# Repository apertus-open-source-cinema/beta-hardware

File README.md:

View this project on [CADLAB.io](https://cadlab.io/project/23633). 

# AXIOM Beta Hardware
[Axiom beta enclosure concept art](https://www.apertus.org/)

This repository contains all the information and files related to the hardware of the AXIOM Beta.

The [AXIOM Beta](https://www.apertus.org/axiom-beta) is an open source, open hardware, professional-grade digital film camera made by [apertus°](https://www.apertus.org/). It is designed to be modular e.g. interchangeable sensor front end etc. and supports recording at 4K resolution.

Introduction to [camera structure](https://www.apertus.org/axiom-beta-modularity).

## Contributing
If you would like to participate in this project, please see the following links:

[apertus° Labs](https://lab.apertus.org/project/view/4/) - Tasks, discussions, etc.
Project [Wiki](https://wiki.apertus.org/index.php/Main_Page) - User manuals, BOMs etc.
Programming languages and contact [methods](https://wiki.apertus.org/index.php/How_to_Contribute).
Useful [Links](https://wiki.apertus.org/index.php/Useful_Links).

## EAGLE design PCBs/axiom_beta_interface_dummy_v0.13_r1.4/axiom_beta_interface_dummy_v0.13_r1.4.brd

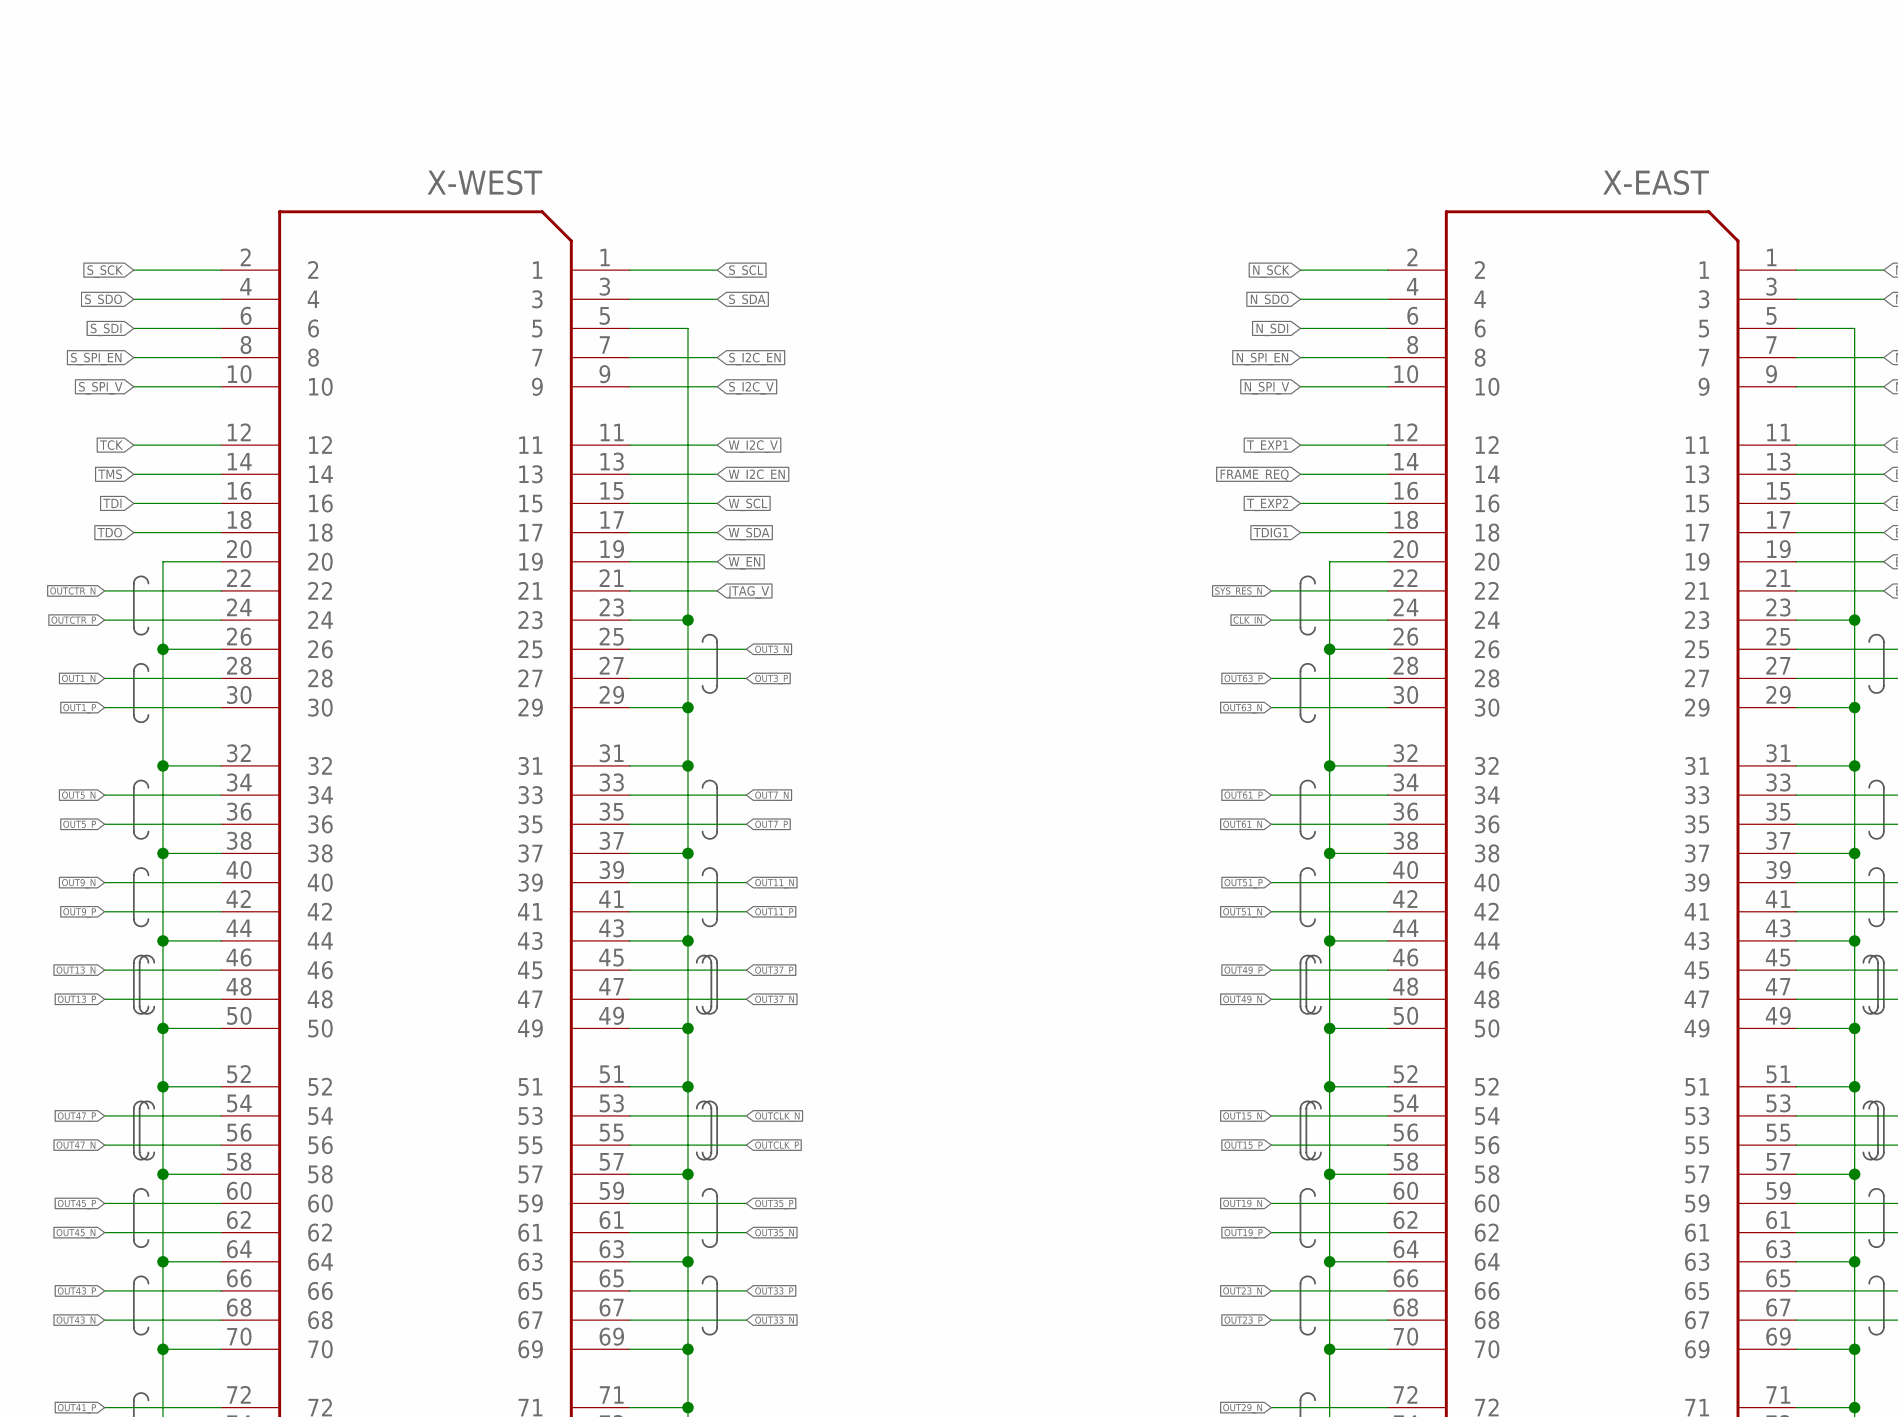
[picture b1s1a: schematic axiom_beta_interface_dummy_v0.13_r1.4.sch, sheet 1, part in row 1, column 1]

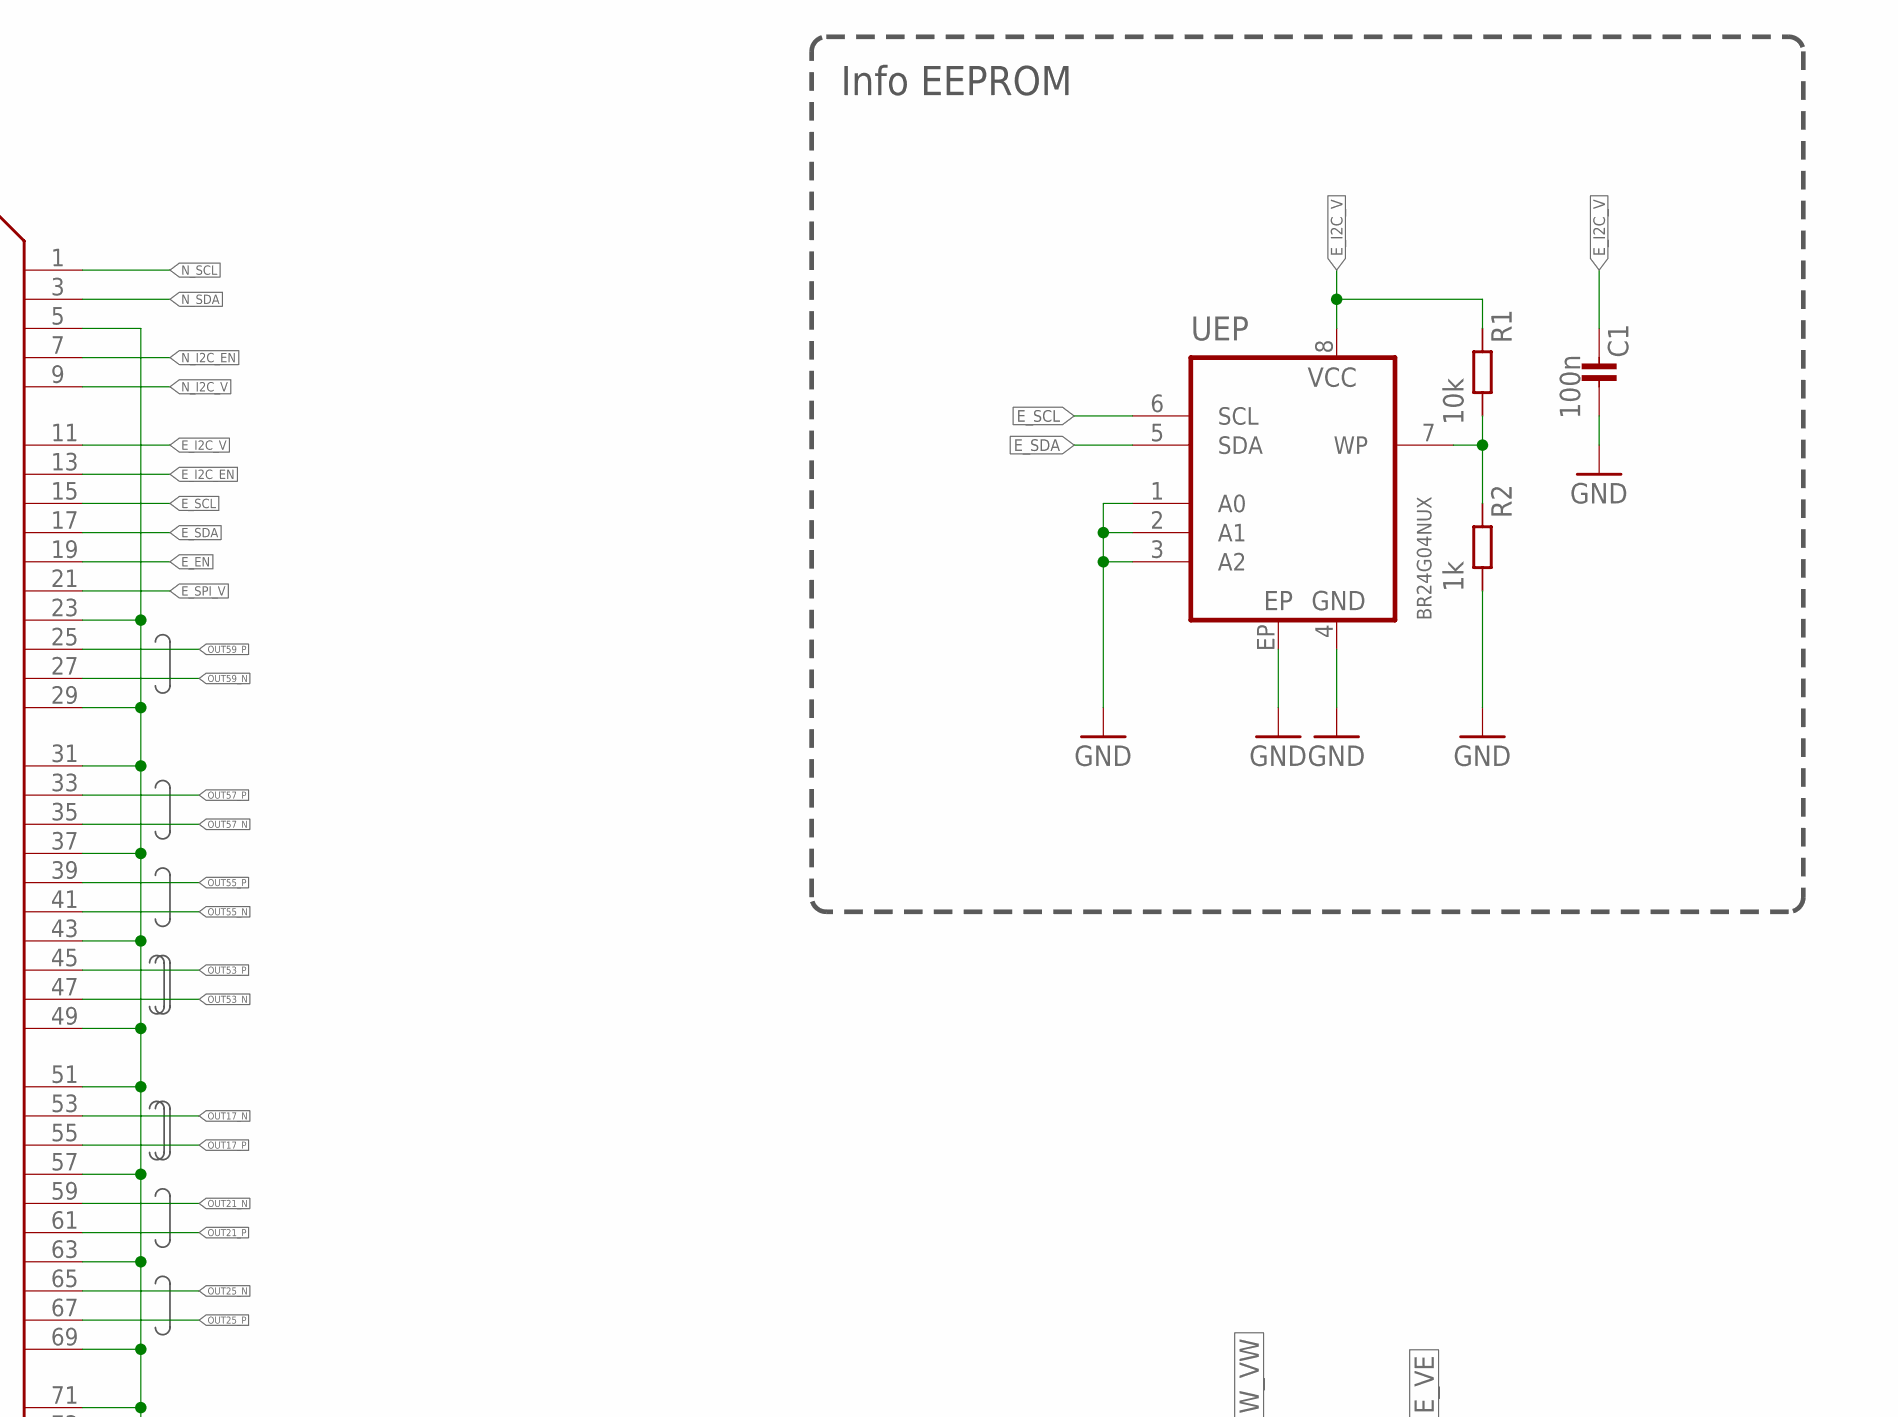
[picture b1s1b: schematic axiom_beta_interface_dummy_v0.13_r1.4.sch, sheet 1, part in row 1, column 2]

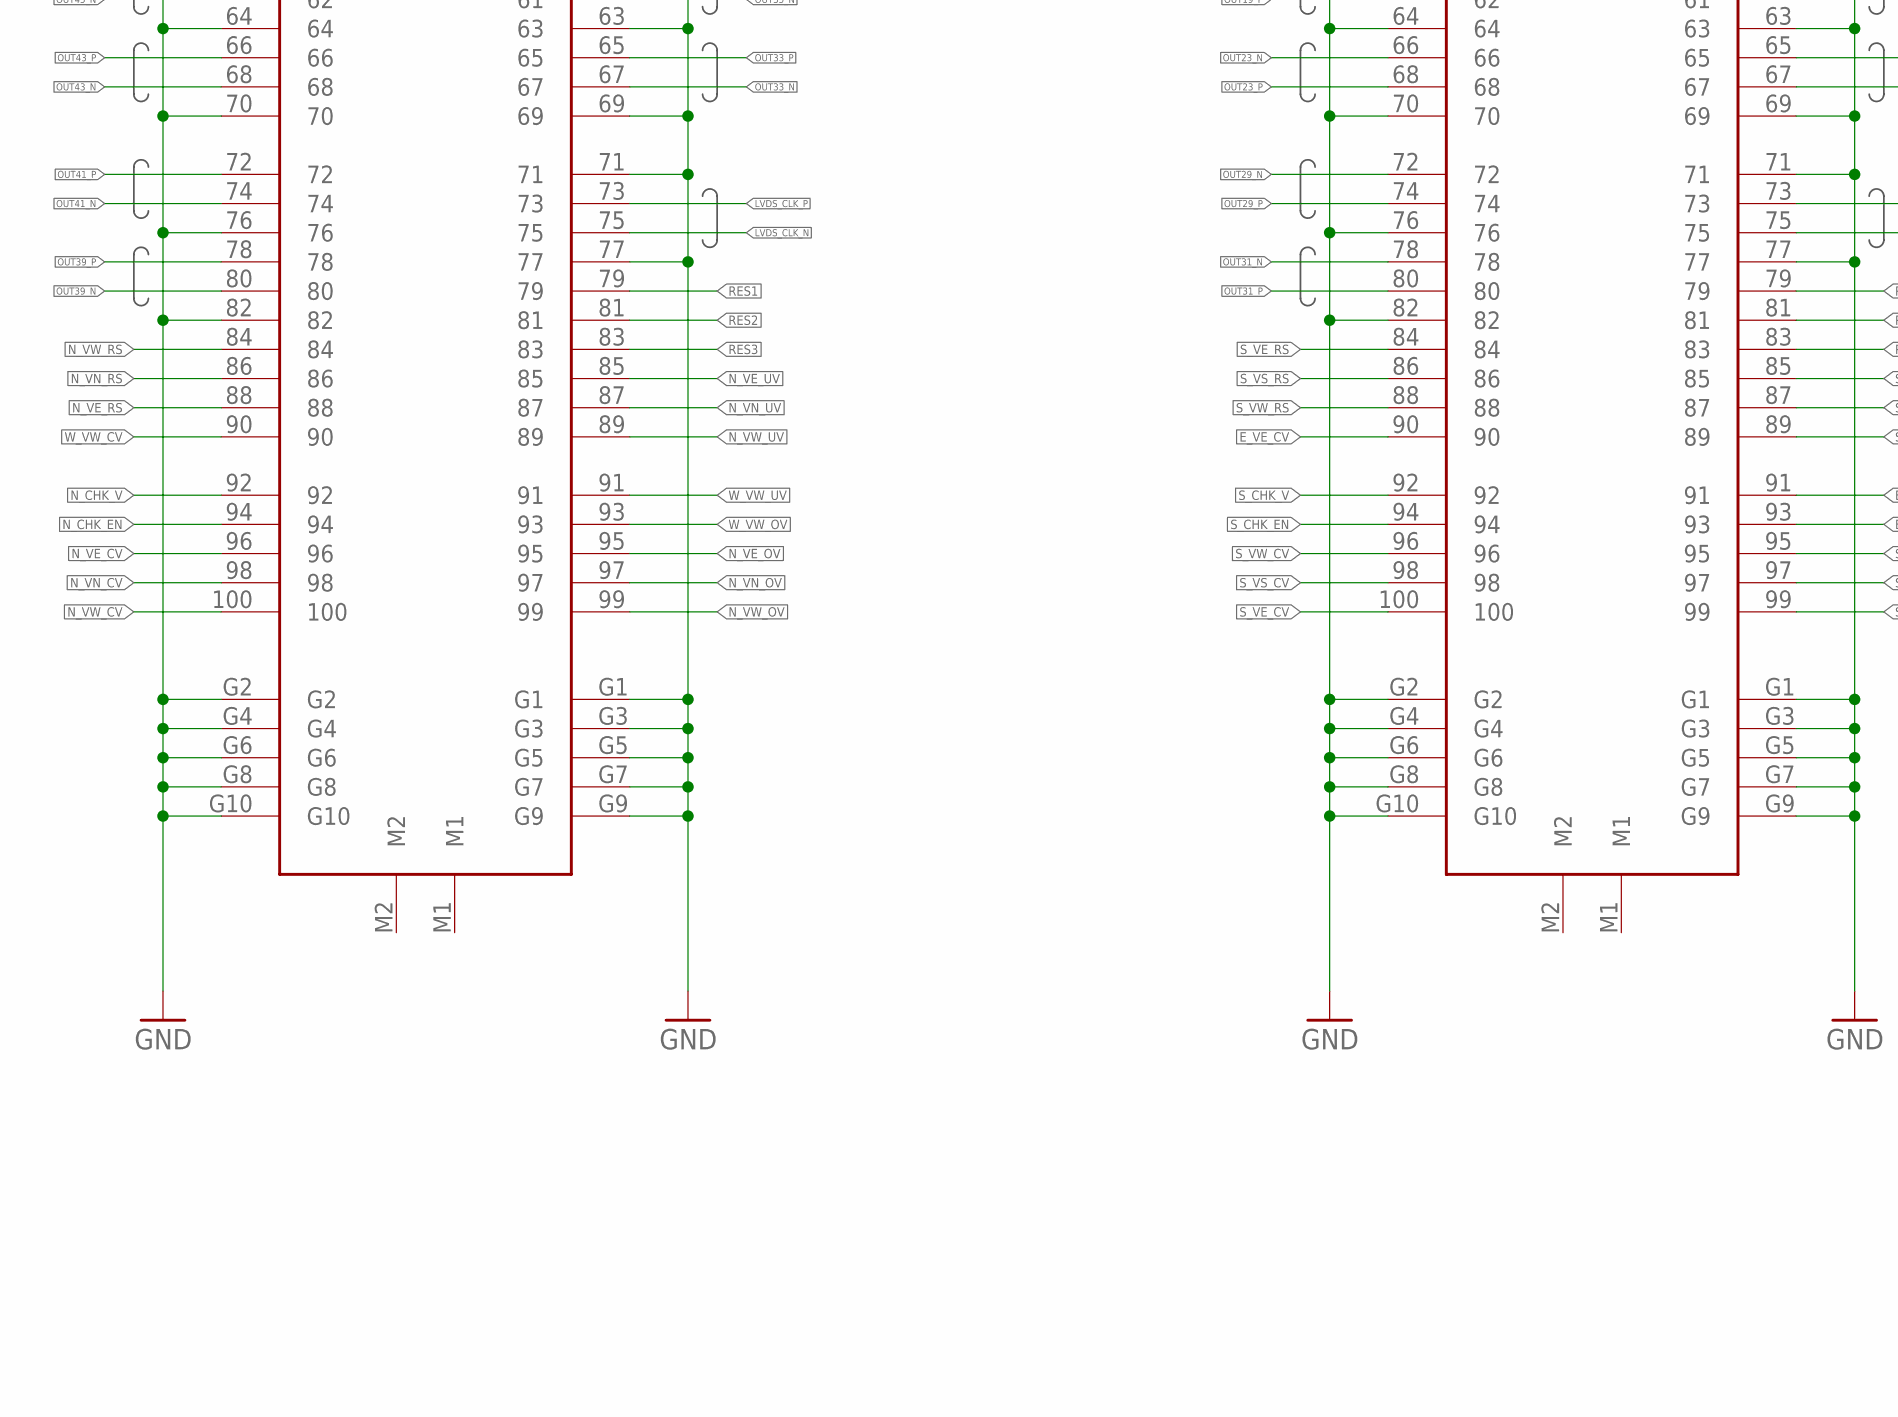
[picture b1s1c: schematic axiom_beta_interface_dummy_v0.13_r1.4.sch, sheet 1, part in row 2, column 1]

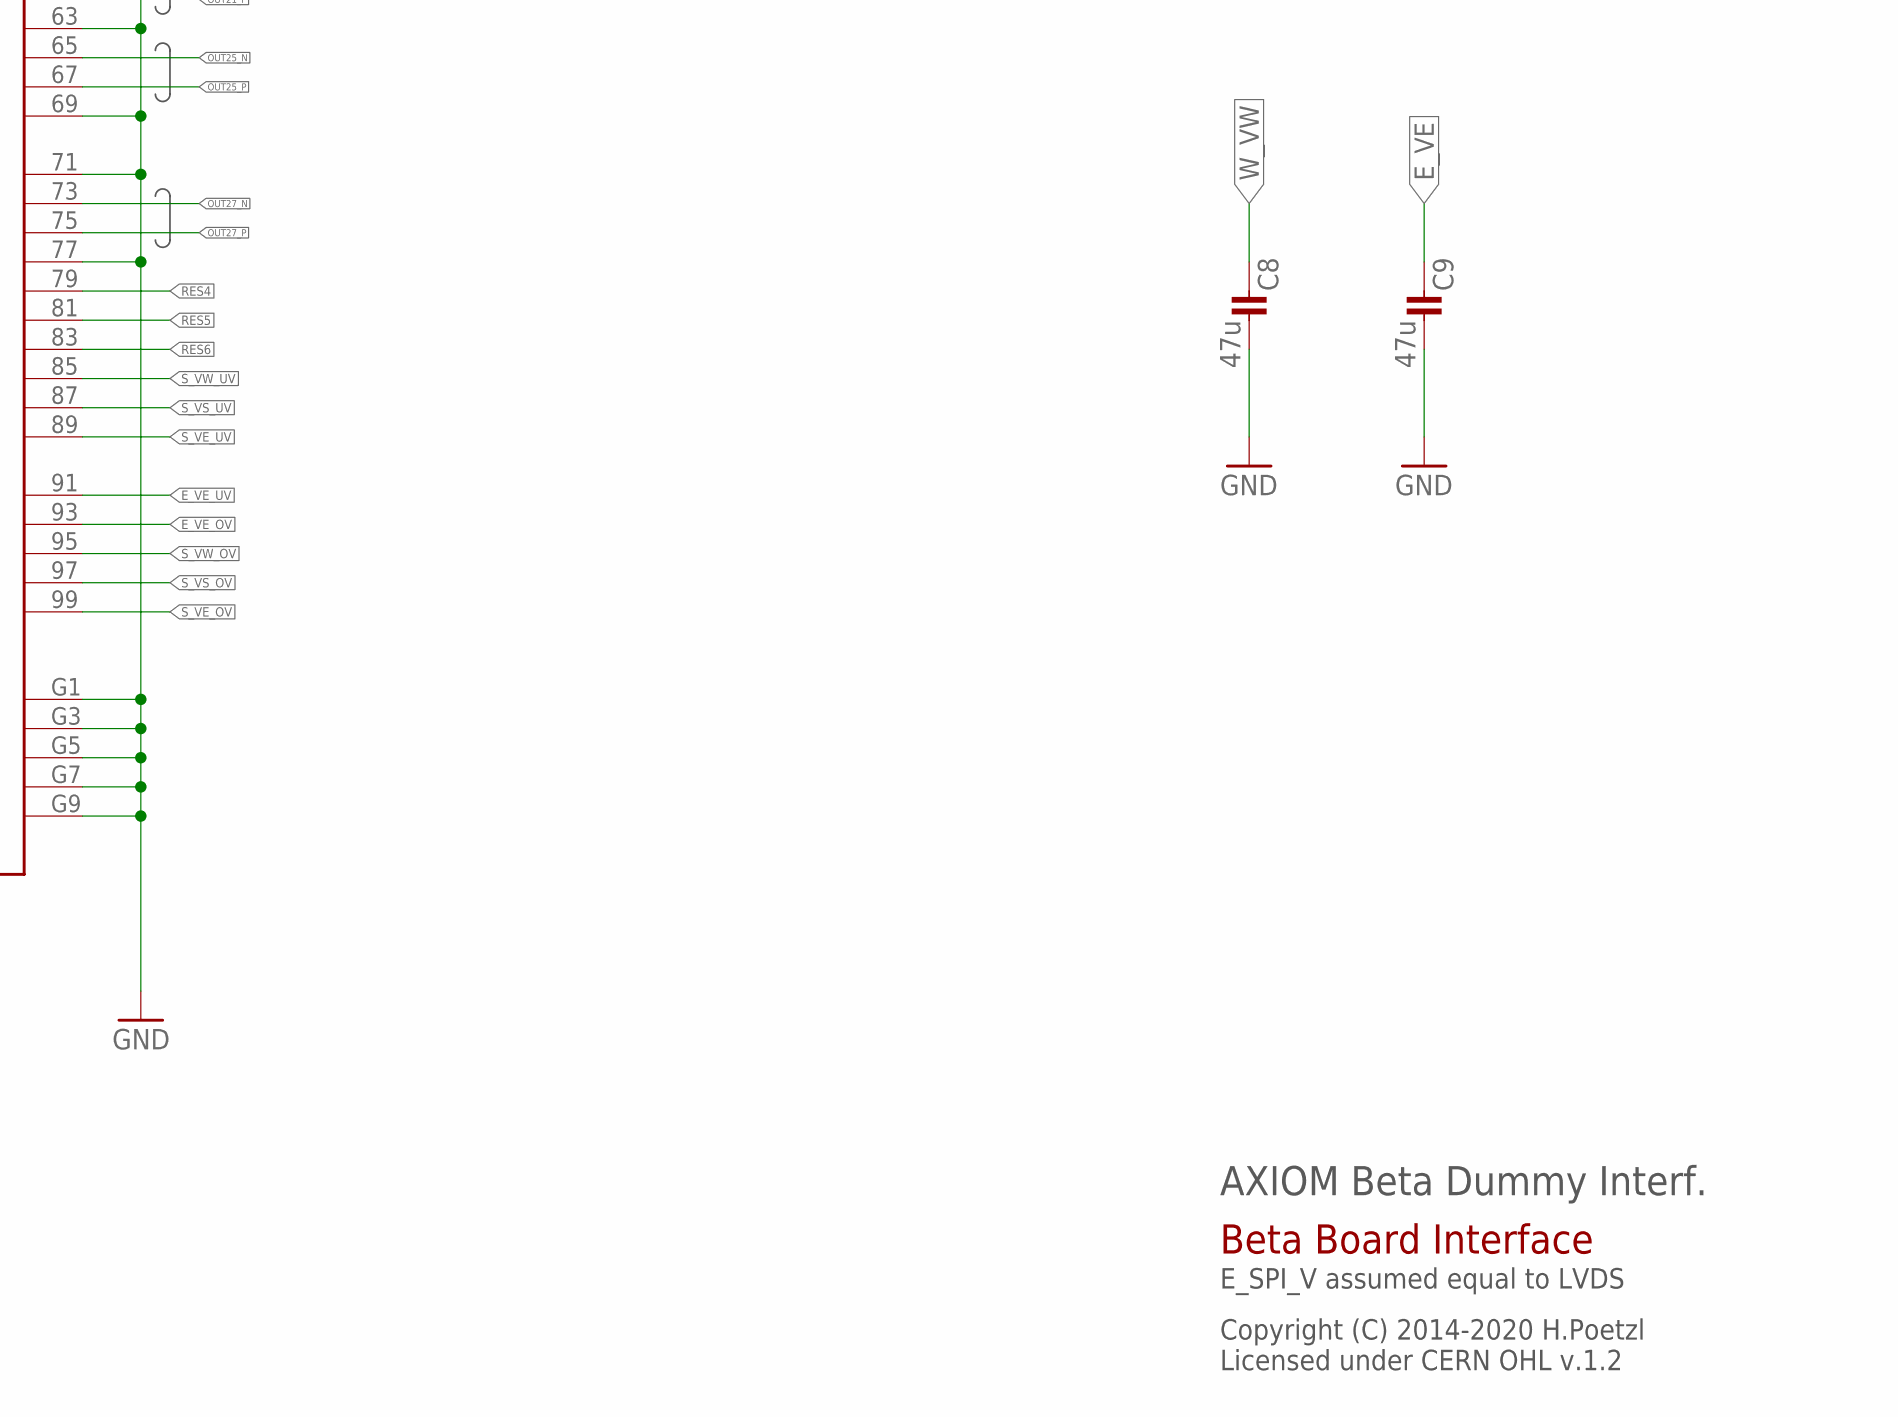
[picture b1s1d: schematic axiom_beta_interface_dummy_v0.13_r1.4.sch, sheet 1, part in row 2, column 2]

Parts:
C1: 100n; 0402-B
C8, C9: 47u; 0805-B
R1: 10k; 0402-B
R2: 1k; 0402-B
UEP: BR24G04NUX; DFN200X300X100-9N
X-EAST: FX10-100/10P; FX10A-100P/10
X-WEST: FX10-100/10P; FX10A-100P/10

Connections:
CLK_IN: X-EAST.24; also elsewhere on the board
E_EN: X-EAST.19
E_I2C_EN: X-EAST.13
E_I2C_V: C1.1, R1.1, UEP.8 (VCC), X-EAST.11
E_SCL: UEP.6 (SCL), X-EAST.15
E_SDA: UEP.5 (SDA), X-EAST.17
E_SPI_V: X-EAST.21
E_VE: C9.1; also elsewhere on the board
E_VE_CV: X-EAST.90
E_VE_OV: X-EAST.93
E_VE_UV: X-EAST.91
FRAME_REQ: X-EAST.14; also elsewhere on the board
GND: C1.2, C8.2, C9.2, R2.2, UEP.1 (A0), UEP.2 (A1), UEP.3 (A2), UEP.4 (GND), UEP.EP, X-EAST.5, X-EAST.20, X-EAST.23, X-EAST.26, X-EAST.29, X-EAST.31, X-EAST.32, X-EAST.37, X-EAST.38, X-EAST.43, X-EAST.44, X-EAST.49, X-EAST.50, X-EAST.51, X-EAST.52, X-EAST.57, X-EAST.58, X-EAST.63, X-EAST.64, X-EAST.69, X-EAST.70, X-EAST.71, X-EAST.76, X-EAST.77, X-EAST.82, X-EAST.G1, X-EAST.G2, X-EAST.G3, X-EAST.G4, X-EAST.G5, X-EAST.G6, X-EAST.G7, X-EAST.G8, X-EAST.G9, X-EAST.G10, X-WEST.5, X-WEST.20, X-WEST.23, X-WEST.26, X-WEST.29, X-WEST.31, X-WEST.32, X-WEST.37, X-WEST.38, X-WEST.43, X-WEST.44, X-WEST.49, X-WEST.50, X-WEST.51, X-WEST.52, X-WEST.57, X-WEST.58, X-WEST.63, X-WEST.64, X-WEST.69, X-WEST.70, X-WEST.71, X-WEST.76, X-WEST.77, X-WEST.82, X-WEST.G1, X-WEST.G2, X-WEST.G3, X-WEST.G4, X-WEST.G5, X-WEST.G6, X-WEST.G7, X-WEST.G8, X-WEST.G9, X-WEST.G10; also elsewhere on the board
JTAG_V: X-WEST.21
LVDS_CLK_N: X-WEST.75; also elsewhere on the board
LVDS_CLK_P: X-WEST.73; also elsewhere on the board
unnamed: R1.2, R2.1, UEP.7 (WP)
N_CHK_EN: X-WEST.94; also elsewhere on the board
N_CHK_V: X-WEST.92; also elsewhere on the board
N_I2C_EN: X-EAST.7; also elsewhere on the board
N_I2C_V: X-EAST.9; also elsewhere on the board
N_SCK: X-EAST.2; also elsewhere on the board
N_SCL: X-EAST.1; also elsewhere on the board
N_SDA: X-EAST.3; also elsewhere on the board
N_SDI: X-EAST.6; also elsewhere on the board
N_SDO: X-EAST.4; also elsewhere on the board
N_SPI_EN: X-EAST.8; also elsewhere on the board
N_SPI_V: X-EAST.10; also elsewhere on the board
N_VE_CV: X-WEST.96; also elsewhere on the board
N_VE_OV: X-WEST.95; also elsewhere on the board
N_VE_RS: X-WEST.88; also elsewhere on the board
N_VE_UV: X-WEST.85; also elsewhere on the board
N_VN_CV: X-WEST.98; also elsewhere on the board
N_VN_OV: X-WEST.97; also elsewhere on the board
N_VN_RS: X-WEST.86; also elsewhere on the board
N_VN_UV: X-WEST.87; also elsewhere on the board
N_VW_CV: X-WEST.100; also elsewhere on the board
N_VW_OV: X-WEST.99; also elsewhere on the board
N_VW_RS: X-WEST.84; also elsewhere on the board
N_VW_UV: X-WEST.89; also elsewhere on the board
OUT1_N: X-WEST.28; also elsewhere on the board
OUT1_P: X-WEST.30; also elsewhere on the board
OUT3_N: X-WEST.25; also elsewhere on the board
OUT3_P: X-WEST.27; also elsewhere on the board
OUT5_N: X-WEST.34; also elsewhere on the board
OUT5_P: X-WEST.36; also elsewhere on the board
OUT7_N: X-WEST.33; also elsewhere on the board
OUT7_P: X-WEST.35; also elsewhere on the board
OUT9_N: X-WEST.40; also elsewhere on the board
OUT9_P: X-WEST.42; also elsewhere on the board
OUT11_N: X-WEST.39; also elsewhere on the board
OUT11_P: X-WEST.41; also elsewhere on the board
OUT13_N: X-WEST.46; also elsewhere on the board
OUT13_P: X-WEST.48; also elsewhere on the board
OUT15_N: X-EAST.54; also elsewhere on the board
OUT15_P: X-EAST.56; also elsewhere on the board
OUT17_N: X-EAST.53; also elsewhere on the board
OUT17_P: X-EAST.55; also elsewhere on the board
OUT19_N: X-EAST.60; also elsewhere on the board
OUT19_P: X-EAST.62; also elsewhere on the board
OUT21_N: X-EAST.59; also elsewhere on the board
OUT21_P: X-EAST.61; also elsewhere on the board
OUT23_N: X-EAST.66; also elsewhere on the board
OUT23_P: X-EAST.68; also elsewhere on the board
OUT25_N: X-EAST.65; also elsewhere on the board
OUT25_P: X-EAST.67; also elsewhere on the board
OUT27_N: X-EAST.73; also elsewhere on the board
OUT27_P: X-EAST.75; also elsewhere on the board
OUT29_N: X-EAST.72; also elsewhere on the board
OUT29_P: X-EAST.74; also elsewhere on the board
OUT31_N: X-EAST.78; also elsewhere on the board
OUT31_P: X-EAST.80; also elsewhere on the board
OUT33_N: X-WEST.67; also elsewhere on the board
OUT33_P: X-WEST.65; also elsewhere on the board
OUT35_N: X-WEST.61; also elsewhere on the board
OUT35_P: X-WEST.59; also elsewhere on the board
OUT37_N: X-WEST.47; also elsewhere on the board
OUT37_P: X-WEST.45; also elsewhere on the board
OUT39_N: X-WEST.80; also elsewhere on the board
OUT39_P: X-WEST.78; also elsewhere on the board
OUT41_N: X-WEST.74; also elsewhere on the board
OUT41_P: X-WEST.72; also elsewhere on the board
OUT43_N: X-WEST.68; also elsewhere on the board
OUT43_P: X-WEST.66; also elsewhere on the board
OUT45_N: X-WEST.62; also elsewhere on the board
OUT45_P: X-WEST.60; also elsewhere on the board
OUT47_N: X-WEST.56; also elsewhere on the board
OUT47_P: X-WEST.54; also elsewhere on the board
OUT49_N: X-EAST.48; also elsewhere on the board
OUT49_P: X-EAST.46; also elsewhere on the board
OUT51_N: X-EAST.42; also elsewhere on the board
OUT51_P: X-EAST.40; also elsewhere on the board
OUT53_N: X-EAST.47; also elsewhere on the board
OUT53_P: X-EAST.45; also elsewhere on the board
OUT55_N: X-EAST.41; also elsewhere on the board
OUT55_P: X-EAST.39; also elsewhere on the board
OUT57_N: X-EAST.35; also elsewhere on the board
OUT57_P: X-EAST.33; also elsewhere on the board
OUT59_N: X-EAST.27; also elsewhere on the board
OUT59_P: X-EAST.25; also elsewhere on the board
OUT61_N: X-EAST.36; also elsewhere on the board
OUT61_P: X-EAST.34; also elsewhere on the board
OUT63_N: X-EAST.30; also elsewhere on the board
OUT63_P: X-EAST.28; also elsewhere on the board
OUTCLK_N: X-WEST.53; also elsewhere on the board
OUTCLK_P: X-WEST.55; also elsewhere on the board
OUTCTR_N: X-WEST.22; also elsewhere on the board
OUTCTR_P: X-WEST.24; also elsewhere on the board
RES1: X-WEST.79
RES2: X-WEST.81
RES3: X-WEST.83
RES4: X-EAST.79
RES5: X-EAST.81
RES6: X-EAST.83
SYS_RES_N: X-EAST.22; also elsewhere on the board
S_CHK_EN: X-EAST.94; also elsewhere on the board
S_CHK_V: X-EAST.92; also elsewhere on the board
S_I2C_EN: X-WEST.7; also elsewhere on the board
S_I2C_V: X-WEST.9; also elsewhere on the board
S_SCK: X-WEST.2; also elsewhere on the board
S_SCL: X-WEST.1; also elsewhere on the board
S_SDA: X-WEST.3; also elsewhere on the board
S_SDI: X-WEST.6; also elsewhere on the board
S_SDO: X-WEST.4; also elsewhere on the board
S_SPI_EN: X-WEST.8; also elsewhere on the board
S_SPI_V: X-WEST.10; also elsewhere on the board
S_VE_CV: X-EAST.100; also elsewhere on the board
S_VE_OV: X-EAST.99; also elsewhere on the board
S_VE_RS: X-EAST.84; also elsewhere on the board
S_VE_UV: X-EAST.89; also elsewhere on the board
S_VS_CV: X-EAST.98; also elsewhere on the board
S_VS_OV: X-EAST.97; also elsewhere on the board
S_VS_RS: X-EAST.86; also elsewhere on the board
S_VS_UV: X-EAST.87; also elsewhere on the board
S_VW_CV: X-EAST.96; also elsewhere on the board
S_VW_OV: X-EAST.95; also elsewhere on the board
S_VW_RS: X-EAST.88; also elsewhere on the board
S_VW_UV: X-EAST.85; also elsewhere on the board
TCK: X-WEST.12
TDI: X-WEST.16
TDIG1: X-EAST.18; also elsewhere on the board
TDO: X-WEST.18
TMS: X-WEST.14
T_EXP1: X-EAST.12; also elsewhere on the board
T_EXP2: X-EAST.16; also elsewhere on the board
W_EN: X-WEST.19
W_I2C_EN: X-WEST.13
W_I2C_V: X-WEST.11
W_SCL: X-WEST.15
W_SDA: X-WEST.17
W_VW: C8.1; also elsewhere on the board
W_VW_CV: X-WEST.90
W_VW_OV: X-WEST.93
W_VW_UV: X-WEST.91

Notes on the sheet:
Info EEPROM
AXIOM Beta Dummy Interf.
Copyright (C) 2014-2020 H.Poetzl Licensed under CERN OHL v.1.2
Beta Board Interface
E_SPI_V assumed equal to LVDS

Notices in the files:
PCBs/axiom_beta_interface_dummy_v0.13_r1.4/axiom_beta_interface_dummy_v0.13_r1.4.brd:
Copyright (C) 2015-2020 H.Pötzl
